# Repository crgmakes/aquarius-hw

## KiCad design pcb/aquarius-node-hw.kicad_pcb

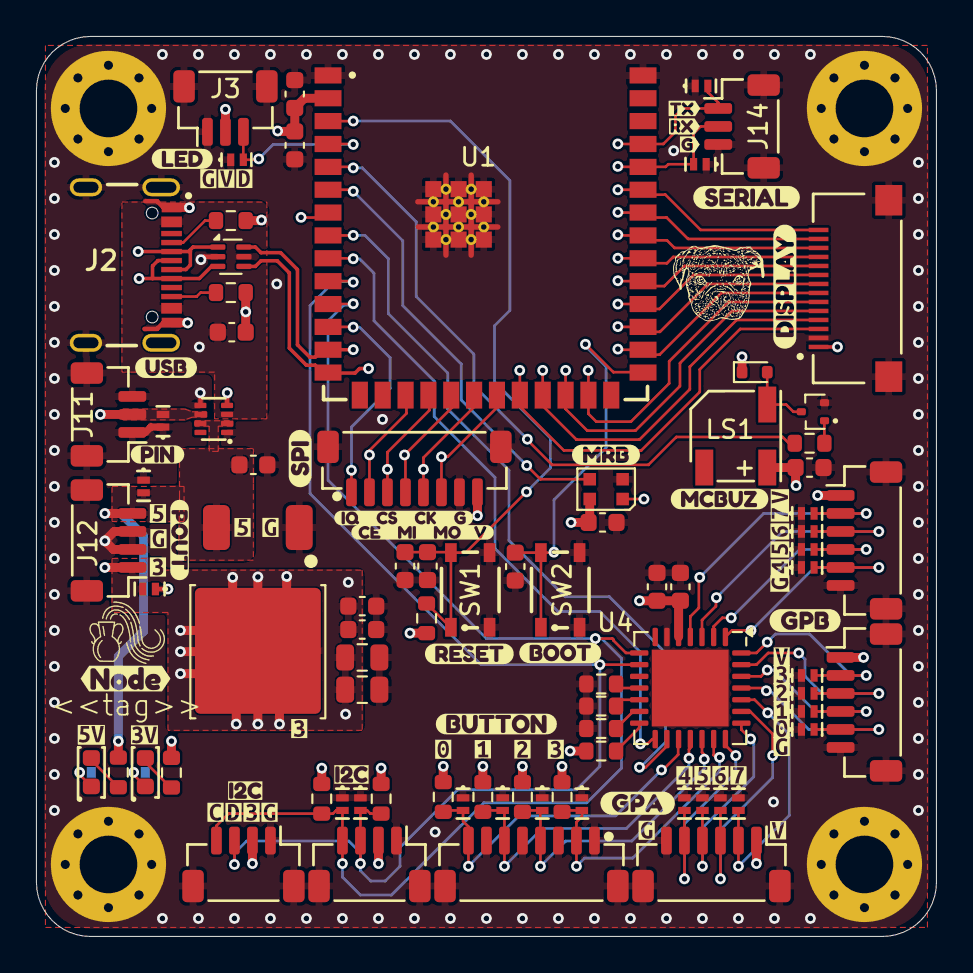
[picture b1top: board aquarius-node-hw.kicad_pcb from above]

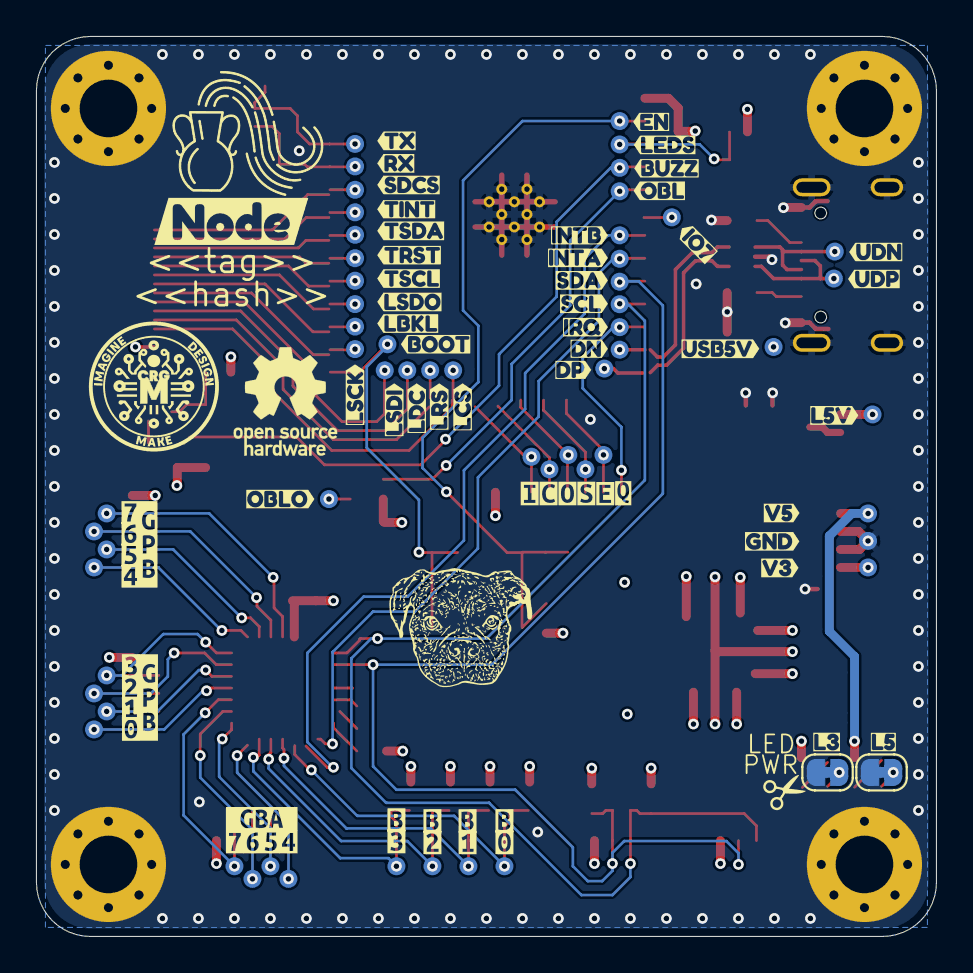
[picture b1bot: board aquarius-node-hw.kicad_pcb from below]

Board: 4 copper layers, 50.0 x 50.0 mm, 275 parts (129 on the bottom side), 68 nets.

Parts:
C1, C4, C5, C6, C7, C9: 0.1uF; C_0603_1608Metric
C2, C11, C12, C13: 10uF; C_0603_1608Metric
C3, C10, C14: 1uF; C_0603_1608Metric
C15, C16: 47uF; C_0805_2012Metric
D1: WS2812B-2020; LED_WS2812B-2020_PLCC4_2.0x2.0mm
D2: D_Schottky; D_SOD-523
D3, D20: PESD5V5C1BL; DFN1006-2
D4, D5, D6, D7, D8, D9, D10, D11, D12, D13, D14, D15, D16, D17, D18, D19, D21, D22, D25, D26, D27, D28: PESD3V3S1BL; DFN1006-2
D23, D24: Orange; LED_0603_1608Metric
H1, H2, H3, H4: MountingHole_3.2mm_M3_Pad_Via
J1: XF2M-1415-1A
J2: USB_C_USB2.0_16P; GCT_USB4105-GF-A
J3, J11, J14: JST_SH_BM03B-SRSS-TB_1x03-1MP_P1.00mm_Vertical
J4, J5, J7: JST_SH_BM06B-SRSS-TB_1x06-1MP_P1.00mm_Vertical
J6, J10: JST_SH_BM08B-SRSS-TB_1x08-1MP_P1.00mm_Vertical
J8, J9, J12: JST_SH_BM04B-SRSS-TB_1x04-1MP_P1.00mm_Vertical
JP1, JP2: SolderJumper-2_P1.3mm_Bridged_RoundedPad1.0x1.5mm
LOGO1: CRGM Logo 7mm
LOGO2: Aquarius Logo 8mm
LOGO3: OSHW-Logo_5.7x6mm_SilkScreen
LOGO4: Aquarius Logo 3.5mm
LOGO5: Roxy 5mm
LOGO6: Roxy 8mm
LS1: FUET-5020; FUET-5025
Q1: MMBT2222A; SOT-523
R1, R2, R15: 4.7K; R_0603_1608Metric
R3, R4, R5, R6, R7, R8, R9, R13, R14: 10K; R_0603_1608Metric
R10, R11: 5.1K; R_0603_1608Metric
R12, R16: 1K; R_0603_1608Metric
SW1, SW2: SKRPABE010; SMD-4P-4.2x3.2mm
TP3, TP4, TP5, TP6, TP7, TP8, TP10, TP12, TP13, TP14, TP15, TP16, TP17, TP18, TP19, TP20, TP21, TP22, TP23, TP24, TP25, TP26, TP27, TP28, TP29, TP30, TP31, TP32, TP33, TP34, TP35, TP36, TP37, TP38, TP39, TP40, TP41, TP42, TP43, TP44, TP45, TP46, TP47, TP48, TP49, TP50, TP51, TP52, TP53, TP54, TP55, TP56, TP57, TP58, TP59, TP60: TestPoint_Pad_D1.0mm
U1: ESP32-S3-WROOM-1-N16R2
U2: LM66200DRLR; SOTFL50P160X60-8N
U3: USBLC6-2P6; SOT-666
U4: MCP23017T-E/ML; QFN-28-1EP_6x6mm_P0.65mm_EP4.25x4.25mm
U7: AZ1084-3.3; TO-252-2
kibuzzard-6A6BB5A6: G***; kibuzzard-6A6BB5A6
kibuzzard-6A6BB9BC: G***; kibuzzard-6A6BB9BC
kibuzzard-6A6BB9C8: G***; kibuzzard-6A6BB9C8
kibuzzard-6A6BB68A: G***; kibuzzard-6A6BB68A
kibuzzard-6A6BB98C: G***; kibuzzard-6A6BB98C
kibuzzard-6A6BB642: G***; kibuzzard-6A6BB642
kibuzzard-6A6BB874: G***; kibuzzard-6A6BB874
kibuzzard-6A6BB995: G***; kibuzzard-6A6BB995
kibuzzard-6A6E221D: G***; kibuzzard-6A6E221D
kibuzzard-6A6E2214: G***; kibuzzard-6A6E2214
kibuzzard-6A189A40: G***; kibuzzard-6A189A40
kibuzzard-68B61F8B: G***; kibuzzard-68B61F8B
kibuzzard-68B61F9F: G***; kibuzzard-68B61F9F
kibuzzard-68B61F47: G***; kibuzzard-68B61F47
kibuzzard-68B61F50: G***; kibuzzard-68B61F50
kibuzzard-68B61F94: G***; kibuzzard-68B61F94
kibuzzard-68B61FA6: G***; kibuzzard-68B61FA6
kibuzzard-68B61FAC: G***; kibuzzard-68B61FAC
kibuzzard-68B621B0, kibuzzard-68B621B0#2: G***; kibuzzard-68B621B0
kibuzzard-68B621B4, kibuzzard-68B621B4#2: G***; kibuzzard-68B621B4
kibuzzard-68B621BA, kibuzzard-68B621BA#2: G***; kibuzzard-68B621BA
kibuzzard-68B621BF, kibuzzard-68B621BF#2: G***; kibuzzard-68B621BF
kibuzzard-68B622AD: G***; kibuzzard-68B622AD
kibuzzard-68B622B6: G***; kibuzzard-68B622B6
kibuzzard-68B622BB: G***; kibuzzard-68B622BB
kibuzzard-68B622C3: G***; kibuzzard-68B622C3
kibuzzard-68B622CC: G***; kibuzzard-68B622CC
kibuzzard-68B622D2: G***; kibuzzard-68B622D2
kibuzzard-68B622DA: G***; kibuzzard-68B622DA
kibuzzard-68B647F5: G***; kibuzzard-68B647F5
kibuzzard-68B6202C: G***; kibuzzard-68B6202C
kibuzzard-68B6218E, kibuzzard-68B6218E#2: G***; kibuzzard-68B6218E
kibuzzard-68B6227B: G***; kibuzzard-68B6227B
kibuzzard-68B6233A: G***; kibuzzard-68B6233A
kibuzzard-68B62172, kibuzzard-68B62172#2: G***; kibuzzard-68B62172
kibuzzard-68B62188, kibuzzard-68B62188#2: G***; kibuzzard-68B62188
kibuzzard-68B62194, kibuzzard-68B62194#2: G***; kibuzzard-68B62194
kibuzzard-68B62237: G***; kibuzzard-68B62237
kibuzzard-68B62271: G***; kibuzzard-68B62271
kibuzzard-68B62276: G***; kibuzzard-68B62276
kibuzzard-68B62285: G***; kibuzzard-68B62285
kibuzzard-68B62319: G***; kibuzzard-68B62319
kibuzzard-68B62347: G***; kibuzzard-68B62347
kibuzzard-68BC4AB6: G***; kibuzzard-68BC4AB6
kibuzzard-68BC4ABA: G***; kibuzzard-68BC4ABA
kibuzzard-68BC4ABE: G***; kibuzzard-68BC4ABE
kibuzzard-68BC4AC2: G***; kibuzzard-68BC4AC2
kibuzzard-68BC4AE6, kibuzzard-68BC4AE6#2: G***; kibuzzard-68BC4AE6
kibuzzard-68BC4B37: G***; kibuzzard-68BC4B37
kibuzzard-68BC5EF2: G***; kibuzzard-68BC5EF2
kibuzzard-68BC5EFE: G***; kibuzzard-68BC5EFE
kibuzzard-68BC5F20: G***; kibuzzard-68BC5F20
kibuzzard-68BC51BC: G***; kibuzzard-68BC51BC
kibuzzard-68BC51CC: G***; kibuzzard-68BC51CC
kibuzzard-68F98705: G***; kibuzzard-68F98705
kibuzzard-699A5D8E: G***; kibuzzard-699A5D8E
kibuzzard-699A5D37: G***; kibuzzard-699A5D37
kibuzzard-699A5D76: G***; kibuzzard-699A5D76
kibuzzard-699A5D82: G***; kibuzzard-699A5D82
kibuzzard-699A5D99: G***; kibuzzard-699A5D99
kibuzzard-699A5DA0: G***; kibuzzard-699A5DA0
kibuzzard-699A5DA6: G***; kibuzzard-699A5DA6
kibuzzard-699A5DD0: G***; kibuzzard-699A5DD0
kibuzzard-699A5DD6: G***; kibuzzard-699A5DD6
kibuzzard-699A5E7B: G***; kibuzzard-699A5E7B
kibuzzard-699A5E80: G***; kibuzzard-699A5E80
kibuzzard-699A5FAD: G***; kibuzzard-699A5FAD
kibuzzard-699A5FC5: G***; kibuzzard-699A5FC5
kibuzzard-699A60EE: G***; kibuzzard-699A60EE
kibuzzard-699A612D: G***; kibuzzard-699A612D
kibuzzard-699A616B: G***; kibuzzard-699A616B
kibuzzard-699A5452: G***; kibuzzard-699A5452
kibuzzard-699A6138: G***; kibuzzard-699A6138
kibuzzard-699A6153: G***; kibuzzard-699A6153
kibuzzard-69437A08: G***; kibuzzard-69437A08
kibuzzard-69437A10: G***; kibuzzard-69437A10
kibuzzard-69437ED8: G***; kibuzzard-69437ED8
kibuzzard-69437FD3: G***; kibuzzard-69437FD3
kibuzzard-683921F2: G***; kibuzzard-683921F2
kibuzzard-690034C9: G***; kibuzzard-690034C9
kibuzzard-690035BE: G***; kibuzzard-690035BE
kibuzzard-690035C9: G***; kibuzzard-690035C9
kibuzzard-694384AE, kibuzzard-694384AE#2, kibuzzard-694384AE#3, kibuzzard-694384AE#4, kibuzzard-694384AE#5: G***; kibuzzard-694384AE
kibuzzard-694384B3, kibuzzard-694384B3#2: G***; kibuzzard-694384B3
kibuzzard-694384E6, kibuzzard-694384E6#2: G***; kibuzzard-694384E6
kibuzzard-694384EB, kibuzzard-694384EB#2: G***; kibuzzard-694384EB
kibuzzard-694384F0, kibuzzard-694384F0#2: G***; kibuzzard-694384F0
kibuzzard-694384F5, kibuzzard-694384F5#2: G***; kibuzzard-694384F5
kibuzzard-6900355C: G***; kibuzzard-6900355C
kibuzzard-6902301E: G***; kibuzzard-6902301E
kibuzzard-6925235D: G***; kibuzzard-6925235D
kibuzzard-6943847F, kibuzzard-6943847F#2: G***; kibuzzard-6943847F
kibuzzard-69003511: G***; kibuzzard-69003511
kibuzzard-69003536: G***; kibuzzard-69003536
kibuzzard-69003541: G***; kibuzzard-69003541
kibuzzard-69003593: G***; kibuzzard-69003593
kibuzzard-69023012: G***; kibuzzard-69023012
kibuzzard-69023019: G***; kibuzzard-69023019
kibuzzard-69438473, kibuzzard-69438473#2, kibuzzard-69438473#3: G***; kibuzzard-69438473
kibuzzard-69438488, kibuzzard-69438488#2: G***; kibuzzard-69438488
kibuzzard-69438491, kibuzzard-69438491#2: G***; kibuzzard-69438491
kibuzzard-69521901: G***; kibuzzard-69521901
kibuzzard-69521908: G***; kibuzzard-69521908

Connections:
+3.3V: C1.1, C2.1, C7.1, C9.1, C10.1, C11.1, C12.1, C14.1, C15.1, C16.1, D1.4 (VDD), D2.1 (K), D26.2 (K2), J1.1, J3.2, J4.1, J5.1, J7.1, J8.2, J9.2, J10.8, J12.1, LS1.2 (+), R1.1, R2.1, R3.1, R4.1, R5.1, R9.1, R13.1, R14.1, R16.1, TP8.1 (1_1), U1.2 (3V3), U4.5 (VDD), U7.2 (VO)
+5V: C13.1, D3.2 (K2), J12.4, R15.1, TP12.1 (1_1), U2.2 (VOUT1), U2.7 (VOUT2), U7.3 (VI)
/MCU/BUZZ_GND: D2.2 (A), LS1.3 (-), Q1.3 (C)
/Peripherals/BTN0: D12.2 (K2), J6.8, R14.2, TP51.1 (1_1), U4.17 (GPA0)
/Peripherals/BTN1: D13.2 (K2), J6.6, R13.2, TP52.1 (1_1), U4.18 (GPA1)
/Peripherals/BTN2: D14.2 (K2), J6.4, R5.2, TP53.1 (1_1), U4.19 (GPA2)
/Peripherals/BTN3: D15.2 (K2), J6.2, R4.2, TP54.1 (1_1), U4.20 (GPA3)
/Peripherals/GPA4: D16.2 (K2), J7.5, TP55.1 (1_1), U4.21 (GPA4)
/Peripherals/GPA5: D17.2 (K2), J7.4, TP56.1 (1_1), U4.22 (GPA5)
/Peripherals/GPA6: D18.2 (K2), J7.3, TP57.1 (1_1), U4.23 (GPA6)
/Peripherals/GPA7: D19.2 (K2), J7.2, TP58.1 (1_1), U4.24 (GPA7)
/Peripherals/GPB0: D4.2 (K2), J4.5, TP43.1 (1_1), U4.25 (GPB0)
/Peripherals/GPB1: D5.2 (K2), J4.4, TP44.1 (1_1), U4.26 (GPB1)
/Peripherals/GPB2: D6.2 (K2), J4.3, TP45.1 (1_1), U4.27 (GPB2)
/Peripherals/GPB3: D7.2 (K2), J4.2, TP46.1 (1_1), U4.28 (GPB3)
/Peripherals/GPB4: D8.2 (K2), J5.5, TP47.1 (1_1), U4.1 (GPB4)
/Peripherals/GPB5: D9.2 (K2), J5.4, TP48.1 (1_1), U4.2 (GPB5)
/Peripherals/GPB6: D10.2 (K2), J5.3, TP49.1 (1_1), U4.3 (GPB6)
/Peripherals/GPB7: D11.2 (K2), J5.2, TP50.1 (1_1), U4.4 (GPB7)
/Peripherals/GPIO_A0: R6.1, U4.11 (A0)
/Peripherals/GPIO_A1: R7.1, U4.12 (A1)
/Peripherals/GPIO_A2: R8.1, U4.13 (A2)
/Peripherals/PIO_RESET: R9.2, U4.14 (~RESET)
/Power/CC1: J2.A5 (CC1), R11.1
/Power/CC2: J2.B5 (CC2), R10.1
/Power/V3.3LED: D24.2 (A), R16.2
/Power/V5LED: D23.2 (A), R15.2
BOOT: C5.1, SW2.1, SW2.2, TP41.1 (1_1), U1.27 (IO0)
BUZZER: R12.1, TP42.1 (1_1), U1.5 (IO5)
D_N: TP25.1 (1_1), U1.13 (USB_D-), U3.6 (I/O1)
D_P: TP26.1 (1_1), U1.14 (USB_D+), U3.4 (I/O2)
EN: C3.1, C4.1, R3.2, SW1.1, SW1.2, TP40.1 (1_1), U1.3 (EN)
GND: C1.2, C2.2, C3.2, C4.2, C5.2, C6.2, C7.2, C9.2, C10.2, C11.2, C12.2, C13.2, C14.2, C15.2, C16.2, D1.2 (VSS), D3.1 (K1), D4.1 (K1), D5.1 (K1), D6.1 (K1), D7.1 (K1), D8.1 (K1), D9.1 (K1), D10.1 (K1), D11.1 (K1), D12.1 (K1), D13.1 (K1), D14.1 (K1), D15.1 (K1), D16.1 (K1), D17.1 (K1), D18.1 (K1), D19.1 (K1), D20.1 (K1), D21.1 (K1), D22.1 (K1), D25.1 (K1), D26.1 (K1), D27.1 (K1), D28.1 (K1), H1.1 (1_1), H2.1 (1_1), H3.1 (1_1), H4.1 (1_1), J1.0, J1.2, J1.15, J2.A1B12 (GND), J2.B1A12 (GND), J2.S1 (SHIELD), J3.0 (MP), J3.1, J3.4 (MP), J4.0 (MP), J4.6, J4.7 (MP), J5.0 (MP), J5.6, J5.7 (MP), J6.0 (MP), J6.1, J6.3, J6.5, J6.7, J6.9 (MP), J7.0 (MP), J7.6, J7.7 (MP), J8.0 (MP), J8.1, J8.5 (MP), J9.0 (MP), J9.1, J9.5 (MP), J10.0 (MP), J10.7, J10.9 (MP), J11.0 (MP), J11.1, J11.3, J11.4 (MP), J12.0 (MP), J12.2, J12.3, J12.5 (MP), J14.0 (MP), J14.3, J14.4 (MP), JP1.1 (A), JP2.1 (A), Q1.2 (E), R6.2, R7.2, R8.2, R10.2, R11.2, SW1.3, SW1.4, SW2.3, SW2.4, TP60.1 (1_1), U1.1 (GND), U1.40 (GND), U1.41 (GND), U2.1 (GND1), U2.4 (~ON), U2.5 (GND2), U3.2 (GND), U4.6 (VSS), U4.29 (EP), U7.1 (GND)
LCD_BL: J1.8, TP18.1 (1_1), U1.29 (IO36)
LCD_CS: J1.3, TP13.1 (1_1), U1.22 (IO14)
LCD_DC: J1.5, TP15.1 (1_1), U1.24 (IO47)
LCD_RS: J1.4, TP14.1 (1_1), U1.23 (IO21)
LCD_SCK: J1.7, TP17.1 (1_1), U1.28 (IO35)
LCD_SDI: J1.6, TP16.1 (1_1), U1.25 (IO48)
LCD_SDO: J1.9, TP19.1 (1_1), U1.30 (IO37)
LEDS: D25.2 (K2), J3.3, TP59.1 (1_1), U1.4 (IO4)
LINE_5V: D20.2 (K2), J11.2, TP10.1 (1_1), U2.6 (VIN2)
unnamed: D23.1 (K), JP1.2 (B)
unnamed: D24.1 (K), JP2.2 (B)
unnamed: Q1.1 (B), R12.2
unnamed: TP7.1 (1_1), U1.7 (IO7)
OBL: D1.3 (DIN), TP39.1 (1_1), U1.6 (IO6)
OBL_OUT: D1.1 (DOUT), TP3.1 (1_1)
PIO_INTA: TP37.1 (1_1), U1.9 (IO16), U4.15 (INTB)
PIO_INTB: TP38.1 (1_1), U1.8 (IO15), U4.16 (INTA)
RX: D28.2 (K2), J14.2, TP30.1 (1_1), U1.36 (RXD0)
SCL: D21.2 (K2), J8.4, J9.4, R2.2, TP6.1 (1_1), U1.11 (IO18), U4.8 (SCK)
SDA: D22.2 (K2), J8.3, J9.3, R1.2, TP5.1 (1_1), U1.10 (IO17), U4.9 (SDA)
SD_CS: J1.14, TP24.1 (1_1), U1.35 (IO42)
SPI_CE0: J10.2, TP32.1 (1_1), U1.17 (IO9)
SPI_CLK: J10.5, TP35.1 (1_1), U1.20 (IO12)
SPI_CS0: J10.3, TP33.1 (1_1), U1.18 (IO10)
SPI_IRQ0: J10.1, TP31.1 (1_1), U1.12 (IO8)
SPI_MISO: J10.4, TP34.1 (1_1), U1.19 (IO11)
SPI_MOSI: J10.6, TP36.1 (1_1), U1.21 (IO13)
TX: D27.2 (K2), J14.1, TP29.1 (1_1), U1.37 (TXD0)
T_INT: J1.13, TP23.1 (1_1), U1.34 (IO41)
T_RESET: J1.11, TP21.1 (1_1), U1.32 (IO39)
T_SCL: J1.10, TP20.1 (1_1), U1.31 (IO38)
T_SDA: J1.12, TP22.1 (1_1), U1.33 (IO40)
USB_5V: C6.1, J2.A4B9 (VBUS), J2.B4A9 (VBUS), TP4.1 (1_1), U2.3 (VIN1), U3.5 (VBUS)
USB_D_N: J2.A7 (D-), J2.B7 (D-), TP27.1 (1_1), U3.1 (I/O1)
USB_D_P: J2.A6 (D+), J2.B6 (D+), TP28.1 (1_1), U3.3 (I/O2)
